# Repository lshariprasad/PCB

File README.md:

# IoT Environmental Monitoring System – Arduino Nano PCB

A multi-sensor environmental monitoring hardware project built around an **Arduino Nano**. The custom PCB brings together temperature, humidity, pressure, light, motion, smoke, and gas-sensing modules, along with an OLED display and a buzzer output.

The hardware schematic, PCB layout, and 3D board preview are designed in **KiCad**. This repository can be used as the project documentation and as a starting point for PCB fabrication, firmware development, assembly, and testing.

> **Project status:** The schematic and PCB layout/3D visualisation are the current design deliverables. Update this README with fabrication, assembly, firmware, and test results after those stages have been completed.

---

## Table of contents

- [Project overview](#project-overview)
- [Features](#features)
- [Hardware components](#hardware-components)
- [System architecture](#system-architecture)
- [Signal and interface list](#signal-and-interface-list)
- [Power and wiring notes](#power-and-wiring-notes)
- [PCB design](#pcb-design)
- [Getting started](#getting-started)
- [Firmware development](#firmware-development)
- [Calibration and testing](#calibration-and-testing)
- [Safety notes](#safety-notes)
- [Repository structure](#repository-structure)
- [Future improvements](#future-improvements)
- [Contributing](#contributing)
- [License](#license)
- [Author](#author)

---

## Project overview

The goal of this project is to create a single PCB that connects an Arduino Nano to several commonly used sensor modules. The Arduino can collect readings from the connected sensors, process the measurements, display information on an OLED, and activate a buzzer when firmware-defined conditions are met.

The board is designed with connectors for the individual modules so that they can be connected, replaced, or tested separately. The PCB layout and 3D preview help check connector placement and the overall board arrangement before fabrication.

### Monitoring modules

| Module | Intended measurement or function | Interface |
|---|---|---|
| DHT22 | Ambient temperature and relative humidity | Digital, single-wire style interface |
| MQ-135 | General air-quality-related gas response | Analog output from sensor module |
| MQ-2 | Smoke and combustible-gas response | Analog output from sensor module |
| BMP280 | Atmospheric pressure and temperature | I²C |
| LDR module | Relative light level | Analog output from module |
| HC-SR501 PIR | Motion detection | Digital output |
| DS18B20 | Contact temperature measurement | 1-Wire |
| OLED display | Displays readings and system information | I²C |
| Buzzer | Audible status or alert output | Digital control |

The MQ-series sensors are broad-response sensors. Their readings require suitable warm-up, calibration, and interpretation; they should not be treated as precise gas-concentration measurements without a validated calibration method.

---

## Features

- Arduino Nano as the central controller.
- Multiple sensor-module connectors on one PCB.
- Separate sensor connections for temperature, humidity, pressure, light, motion, smoke, and gas-response measurements.
- I²C connection for the BMP280 and OLED display.
- Dedicated buzzer control connection.
- PCB schematic and board layout created in KiCad.
- 3D PCB visualisation for checking component and connector placement.
- Modular connectors to simplify sensor replacement and troubleshooting.

---

## Hardware components

| No. | Component | Quantity | Purpose |
|---:|---|---:|---|
| 1 | Arduino Nano | 1 | Main microcontroller |
| 2 | DHT22 module | 1 | Temperature and humidity sensing |
| 3 | MQ-135 module | 1 | General air-quality-related gas response |
| 4 | MQ-2 module | 1 | Smoke/combustible-gas response |
| 5 | BMP280 module | 1 | Pressure and temperature sensing |
| 6 | LDR light-sensor module | 1 | Light-level sensing |
| 7 | HC-SR501 PIR module | 1 | Motion detection |
| 8 | DS18B20 sensor | 1 | Contact temperature sensing |
| 9 | OLED display module | 1 | Local display |
| 10 | Buzzer | 1 | Audible alert/status output |
| 11 | 10 kΩ resistor | 1 | DHT22 data-line pull-up, as shown in the schematic |
| 12 | 4.7 kΩ resistor | 1 | DS18B20 data-line pull-up, as shown in the schematic |
| 13 | PCB headers/connectors | As required | Sensor and module connections |

**Note:** Confirm the exact module variants, connector pin order, resistor values, footprints, and quantities against the KiCad schematic and BOM before ordering parts or fabricating the PCB. Some sensor modules are sold in multiple pinout and voltage variants.

---

## System architecture

```text
                     +----------------------+
                     |     Arduino Nano     |
                     |   Main Controller    |
                     +----------+-----------+
                                |
       +------------------------+-------------------------+
       |             |          |          |               |
       v             v          v          v               v
    DHT22         DS18B20     HC-SR501   LDR module     MQ-135 / MQ-2
  Temp/RH         Temp        Motion     Light level   Gas/smoke response
       |             |          |          |               |
       +-------------+----------+----------+---------------+
                                |
                         I²C bus / outputs
                                |
                       +--------+--------+
                       |                 |
                       v                 v
                   BMP280          OLED display
                 Pressure/temp     Readout/status
                                |
                                v
                             Buzzer
                          Audio alert
```

The diagram is a functional overview, not a substitute for the actual schematic. Use the KiCad schematic as the source of truth for electrical connections and pin assignments.

---

## Signal and interface list

The schematic uses the following signal names. Match the firmware to the final net-to-pin assignments in the KiCad schematic.

| Schematic net name | Connected module | Purpose |
|---|---|---|
| `DHT_DATA` | DHT22 | Temperature/humidity data |
| `DS18B20_DATA` | DS18B20 | 1-Wire temperature data |
| `PIR_OUT` | HC-SR501 | Digital motion-detection output |
| `BUZZER_CTRL` | Buzzer | Buzzer control |
| `MQ135_AO` | MQ-135 | Analog sensor output |
| `MQ2_AO` | MQ-2 | Analog sensor output |
| `LDR_AO` | LDR module | Analog light-level output |
| `I2C_SDA` | BMP280 and OLED | I²C data line |
| `I2C_SCL` | BMP280 and OLED | I²C clock line |

**Important:** The table intentionally lists schematic net names rather than guessed Arduino pin numbers. Check the schematic before writing firmware or connecting a module. Confirm that the physical connector pin order is `VCC`, `GND`, and signal (or the order actually printed in the schematic); never assume all modules use the same order.

---

## Power and wiring notes

- Follow the power-net labels in the KiCad schematic. The design includes **+5 V** and **+3.3 V** connections; do not interchange them.
- Connect all module grounds to the board's common ground as shown in the schematic.
- Check the voltage requirements and logic levels of each exact breakout/module before connecting it.
- The BMP280 IC itself is a 3.3 V device. Some breakout boards include a regulator and/or level shifting, while others do not. Verify the specific module before connecting it to a 5 V Arduino Nano I²C bus. Add suitable I²C level shifting when required.
- MQ sensor modules contain heater elements and can draw considerably more current than simple digital sensors. Provide a suitable regulated supply with adequate current capacity; do not assume the Arduino Nano's onboard regulator can power every module.
- Check polarity and connector pin order before applying power.
- Keep sensor power and signal wiring within the voltage/current limits of the modules and the Arduino Nano.

---

## PCB design

The PCB was designed in **KiCad**. The design workflow includes:

1. Creating the circuit schematic and assigning net labels.
2. Assigning footprints to the Arduino Nano and module connectors.
3. Placing the connectors and routing the PCB tracks.
4. Checking the board outline, clearances, and connector positions.
5. Reviewing the board in KiCad's 3D Viewer.

### Design files

Add the KiCad project files to the repository and update these paths to match your actual filenames:

- `hardware/` – KiCad project files.
- `hardware/*.kicad_pro` – project settings.
- `hardware/*.kicad_sch` – circuit schematic.
- `hardware/*.kicad_pcb` – PCB layout.
- `hardware/*.kicad_dru` – design rules, if used.
- `hardware/fabrication/` – Gerber, drill, and fabrication outputs, once generated.

Before fabrication, run the Electrical Rules Checker (ERC) and Design Rules Checker (DRC), review all warnings, and verify connector footprints and pin numbering against the physical modules.

---

## Getting started

### 1. Install KiCad

Install a recent stable version of KiCad from the official website:

https://www.kicad.org/download/

### 2. Clone or download this repository

```bash
git clone https://github.com/<your-username>/<your-repository-name>.git
cd <your-repository-name>
```

Replace the placeholder URL with your actual GitHub repository URL.

### 3. Open the PCB design

1. Open KiCad.
2. Open the `.kicad_pro` project file from the `hardware/` folder.
3. Open the schematic editor to inspect circuit connections.
4. Open the PCB Editor to inspect component placement and routing.
5. Open the 3D Viewer to inspect the board's 3D representation.

### 4. Check before fabrication

- Run ERC on the schematic.
- Run DRC on the PCB.
- Confirm all footprints and connector pin numbering.
- Check board dimensions, mounting requirements, clearances, and copper widths.
- Verify supply rails and current capacity, especially for the MQ sensor modules.
- Generate Gerber and drill files only after the design checks are complete.

---

## Firmware development

The Arduino Nano is intended to read the sensor modules and manage the OLED and buzzer. Add the firmware source code to a `firmware/` directory when it is ready.

A typical firmware structure could look like this:

```text
firmware/
└── environmental_monitor/
    ├── environmental_monitor.ino
    └── README.md
```

### Suggested firmware behaviour

1. Initialise the sensor modules and OLED display.
2. Read temperature and humidity from the DHT22.
3. Read temperature from the DS18B20.
4. Read pressure and temperature from the BMP280 over I²C.
5. Read analog values from the MQ-135, MQ-2, and LDR modules.
6. Read the digital output from the HC-SR501 PIR module.
7. Display available readings and motion/status information on the OLED.
8. Activate the buzzer according to configurable thresholds or events.

### Possible Arduino libraries

Choose library versions compatible with your installed Arduino IDE and the exact sensor modules:

- Adafruit BMP280 Library (BMP280)
- Adafruit Unified Sensor (when required by the selected Adafruit library)
- DHT sensor library (DHT22)
- OneWire (DS18B20)
- DallasTemperature (DS18B20)
- Adafruit SSD1306 or U8g2 (OLED, depending on the display controller)

The MQ-135 and MQ-2 analog outputs can be read using the Arduino analog-input functions. Converting raw readings into meaningful gas estimates requires sensor-specific calibration and a suitable measurement model.

---

## Calibration and testing

Test one module at a time before testing the complete system.

| Test | What to verify |
|---|---|
| Power rails | Measure the expected +5 V and +3.3 V rails before inserting modules |
| Arduino Nano | Confirm that the Nano powers up and can upload a basic test sketch |
| DHT22 | Compare temperature and humidity readings with a reference instrument |
| DS18B20 | Check the 1-Wire connection and compare readings with a reference thermometer |
| BMP280 | Confirm I²C detection and check pressure/temperature readings |
| OLED | Confirm display initialisation and readable output |
| LDR | Check that the analog reading changes between bright and dark conditions |
| PIR | Check motion detection and allow for the module's settling/initialisation time |
| MQ-135 / MQ-2 | Allow the required preheating period and follow the module datasheet's calibration guidance |
| Buzzer | Confirm that the control signal activates the buzzer as intended |
| Complete board | Check for unexpected heating, unstable readings, resets, or power-supply problems |

Record the test date, supply voltage, sensor/module variant, calibration method, and observed results. Do not publish unverified accuracy figures.

---

## Safety notes

- This is an educational electronics project, not a certified environmental, industrial, or life-safety instrument.
- MQ-2 and MQ-135 modules are not substitutes for certified smoke, fire, carbon-monoxide, or hazardous-gas alarms.
- Do not use this project as the only protection against fire, gas leaks, or unsafe air conditions.
- MQ sensor readings are affected by warm-up time, temperature, humidity, sensor age, and other gases. They are not automatically equivalent to calibrated ppm values.
- Use a properly rated power supply and avoid short circuits or reversed polarity.
- Disconnect power before changing wiring or modifying the PCB.

---

## Repository structure

A suggested GitHub structure is:

```text
IoT-Environmental-Monitoring-PCB/
│
├── hardware/
│   ├── schematic/          # KiCad schematic files
│   ├── pcb/                # KiCad PCB layout files
│   ├── libraries/          # Project-specific symbols/footprints, if any
│   ├── fabrication/        # Gerber and drill files (after design validation)
│   └── 3d-models/           # Additional 3D models, if required
│
├── firmware/
│   └── environmental_monitor/
│       └── environmental_monitor.ino
│
├── images/
│   ├── schematic.png
│   ├── pcb-layout.png
│   └── pcb-3d-view.png
│
├── docs/
│   ├── bill-of-materials.md
│   └── test-results.md
│
├── README.md
└── LICENSE
```

Keep only folders and files that actually exist in your repository. Add your schematic, PCB layout, and 3D-view screenshots to `images/` and use the following Markdown to display them (update filenames as needed):

```md
## Project images

### Circuit schematic

### PCB layout

### PCB 3D view

```

---

## Future improvements

- Complete PCB fabrication and physical assembly.
- Develop and upload the Arduino Nano firmware.
- Add a structured OLED screen layout for sensor readings and system status.
- Implement configurable buzzer alerts.
- Calibrate the MQ sensor modules using an appropriate documented procedure.
- Perform individual sensor tests and complete-board validation.
- Add an enclosure and mounting provisions, if required.
- Add data logging or wireless connectivity in a future version, if required.

---

## Contributing

Suggestions, bug reports, and improvements are welcome. To contribute:

1. Fork the repository.
2. Create a feature branch.
3. Make your changes and document any hardware or firmware updates.
4. Test the changes where possible.
5. Submit a pull request with a clear description and relevant screenshots.

For hardware changes, include updated KiCad files and note any changes to component values, footprints, connector pinouts, or power requirements.

---

## License

Choose and add a license before sharing or accepting contributions. For example, hardware designs may use the **CERN Open Hardware Licence**, while firmware/software may use an appropriate open-source software licence. Do not claim a license until its license file has been added to this repository.

---

## Author

**Hari Prasad L S**  
EEE Student | Embedded Systems | IoT | PCB Design

- GitHub: https://github.com/lshariprasad

---

⭐ If you find this project useful, consider starring the repository and sharing your feedback!

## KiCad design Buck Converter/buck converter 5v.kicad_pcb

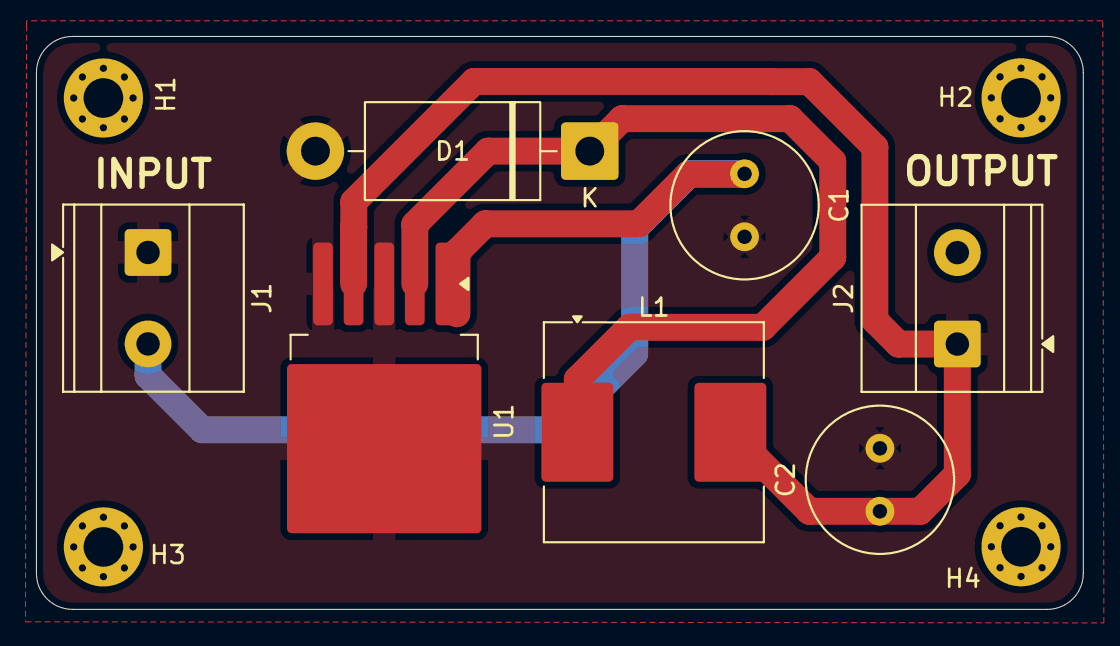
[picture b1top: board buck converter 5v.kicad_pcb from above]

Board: 2 copper layers, 58.2 x 31.8 mm, 11 parts (0 on the bottom side), 4 nets.

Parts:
C1: 470uF 50v; C_Radial_D8.0mm_H7.0mm_P3.50mm
C2: 330uF 25v; C_Radial_D8.0mm_H7.0mm_P3.50mm
D1: 1N5820; D_DO-201AD_P15.24mm_Horizontal
H1, H2, H3, H4: MountingHole_2.2mm_M2_Pad_Via
J1: INPUT; TerminalBlock_Phoenix_MKDS-1,5-2-5.08_1x02_P5.08mm_Horizont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
J2: OUTPUT; TerminalBlock_Phoenix_MKDS-1,5-2-5.08_1x02_P5.08mm_Horizont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
L1: 33uH; L_Coilcraft_MSS1278H-XXX
U1: LM2596S-5; TO-263-5_TabPin3

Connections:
+5V: C2.1, J2.2, L1.2, U1.4 (FB)
+12V: C1.1, J1.2, U1.1 (VIN)
GND: C1.2, C2.2, D1.2 (A), J1.1, J2.1, U1.3 (GND), U1.5 (~ON/OFF)
unnamed: D1.1 (K), L1.1, U1.2 (OUT)

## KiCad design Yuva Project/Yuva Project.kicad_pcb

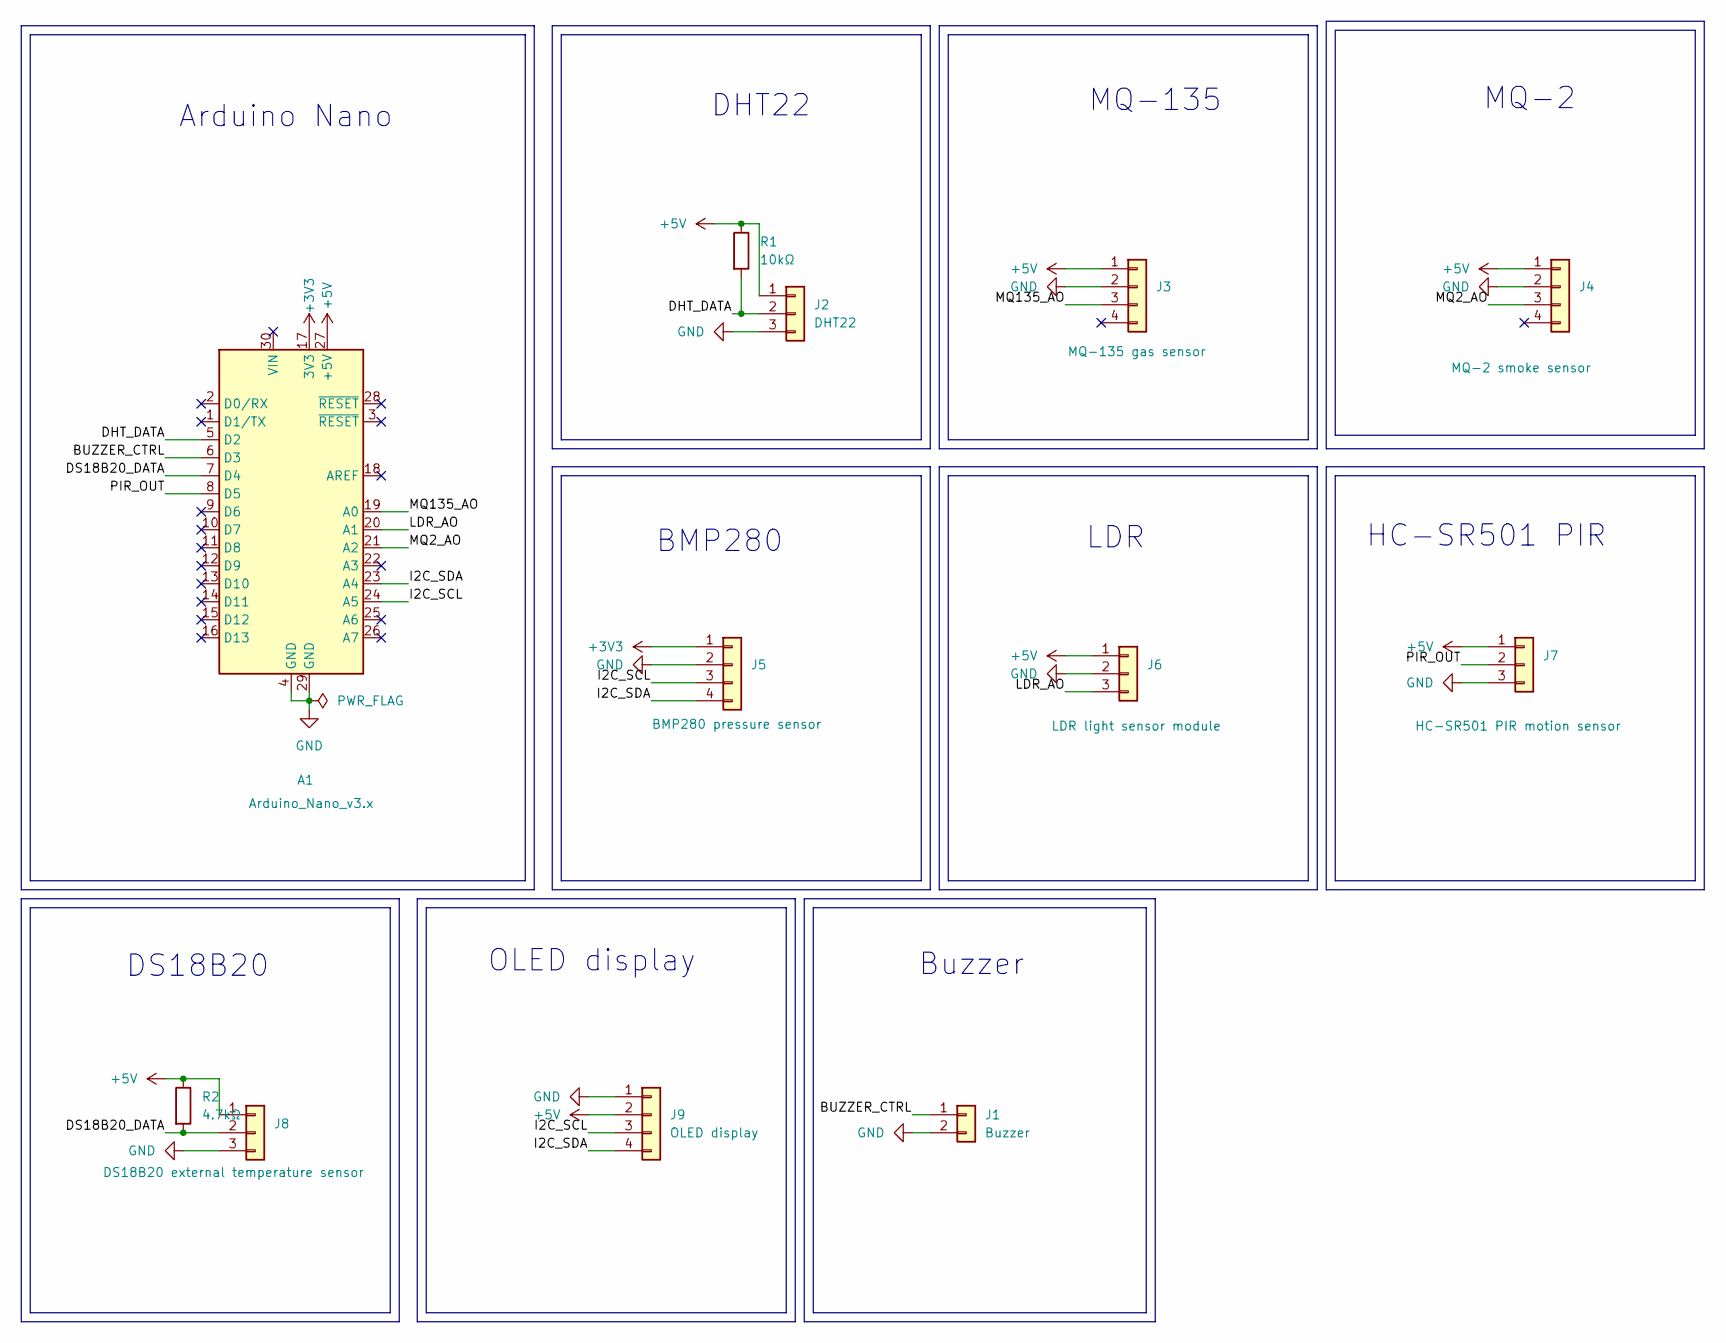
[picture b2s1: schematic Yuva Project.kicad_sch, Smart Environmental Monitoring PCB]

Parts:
A1: Arduino_Nano_v3.x; Arduino_Nano
J1: Buzzer; PinHeader_1x02_P2.54mm_Vertical
J2: DHT22; PinHeader_1x03_P2.54mm_Vertical
J3: MQ-135 gas sensor; PinHeader_1x04_P2.54mm_Vertical
J4: MQ-2 smoke sensor; PinHeader_1x04_P2.54mm_Vertical
J5: BMP280 pressure sensor; PinHeader_1x04_P2.54mm_Vertical
J6: LDR light sensor module; PinHeader_1x03_P2.54mm_Vertical
J7: HC-SR501 PIR motion sensor; PinHeader_1x03_P2.54mm_Vertical
J8: DS18B20 external temperature sensor; PinHeader_1x03_P2.54mm_Vertical
J9: OLED display; PinHeader_1x04_P2.54mm_Vertical
R1: 10kΩ; R_0805_2012Metric
R2: 4.7kΩ; R_0805_2012Metric

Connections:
+3V3: A1.17 (3V3), J5.1
+5V: A1.27 (+5V), J2.1, J3.1, J4.1, J6.1, J7.1, J8.1, J9.2, R1.1, R2.1
/BUZZER_CTRL: A1.6 (D3), J1.1
/DHT_DATA: A1.5 (D2), J2.2, R1.2
/DS18B20_DATA: A1.7 (D4), J8.2, R2.2
/I2C_SCL: A1.24 (A5), J5.3, J9.3
/I2C_SDA: A1.23 (A4), J5.4, J9.4
/LDR_AO: A1.20 (A1), J6.3
/MQ2_AO: A1.21 (A2), J4.3
/MQ135_AO: A1.19 (A0), J3.3
/PIR_OUT: A1.8 (D5), J7.2
GND: A1.4 (GND), A1.29 (GND), J1.2, J2.3, J3.2, J4.2, J5.2, J6.2, J7.3, J8.3, J9.1

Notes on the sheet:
MQ-135
HC-SR501 PIR
DS18B20
Arduino Nano
LDR
OLED display
MQ-2
DHT22
BMP280
Buzzer

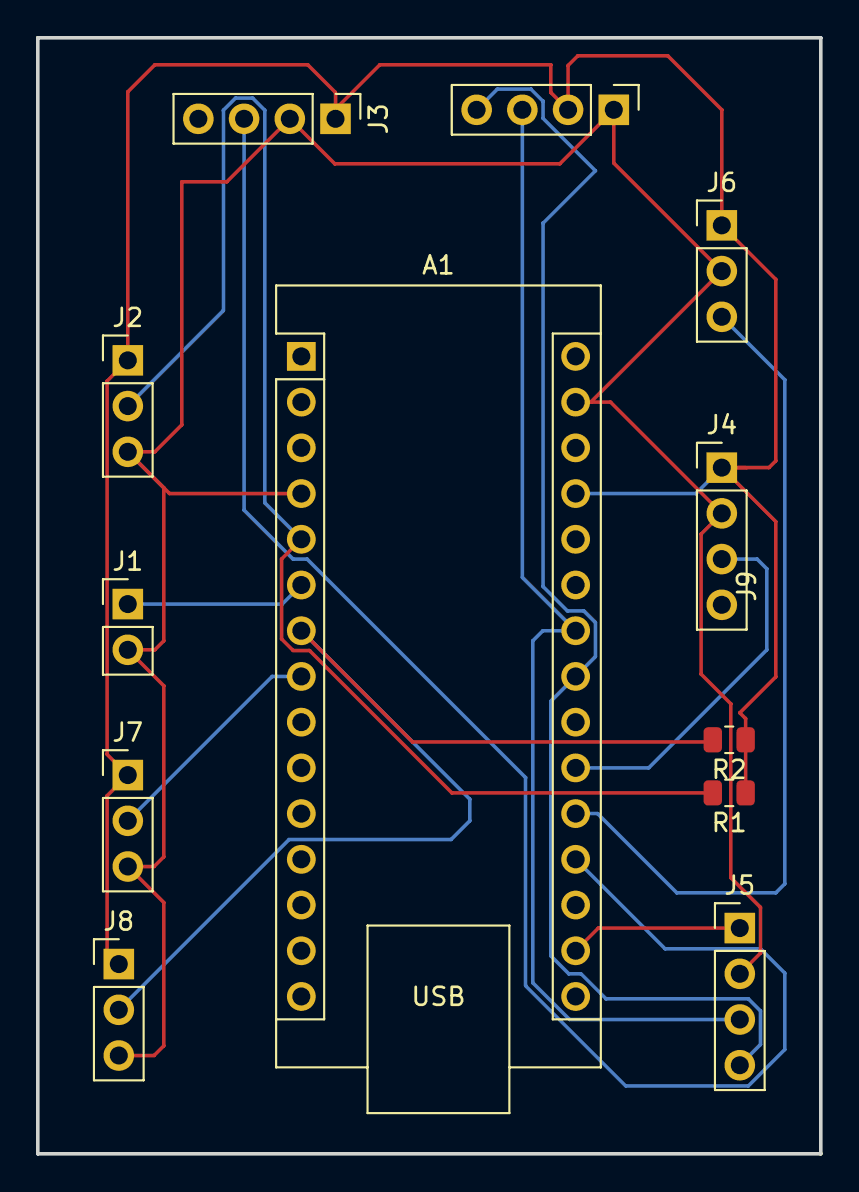
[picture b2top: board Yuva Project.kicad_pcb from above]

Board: 2 copper layers, 43.5 x 62.0 mm, 12 parts (0 on the bottom side), 12 nets.
